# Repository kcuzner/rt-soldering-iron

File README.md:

# RT Soldering Iron
By Kevin Cuzner

**NOTE: THIS IS A WORK IN PROGRESS AND MAY NEVER BE COMPLETED**

## Objective

The Weller RT Soldering Iron Tips are $20-$30 apiece. They are rated to about
55W and many variants come to a very fine point. I had the pleasure of using one
of these soldering irons at my university, but the base stations cost several
hundred dollars. This project aims to build a "base station" of sorts for these
tips so that I can use them without needing to purchase a real base station.

Note that this project has been done before, but I'm doing it myself because
reasons.

## Concept

- The Weller RT soldering iron tips have a 1/8" audio plug which has ground,
  heater, and thermocouple contacts.
- The heater can be powered from 12V and will consume 55W.
- Without closed loop control, the soldering iron tip will quickly burn itself
  up.
- This driver board will provide 12V and closed loop heater control.
- The driver board has a 1/8" audio jack on one end and a barrel jack on the
  other. It is short enough and skinny enough so that it can be mounted directly
  to the tip and become part of the handpiece, with the barrel jack connecting
  to the 12V power supply.

## Builds

### Rev A Deviations

### Rev B Deviations

- 490-14603-1-ND (0.1uF 0402 25V 10% cap) was unavailable. No lead time.
  Ordered 490-13341-1-ND (0.1uf 0402 25V 20% cap) instead.
- Accelerometer was out of stock (again...). The other variant used on the LED
  watch was out of stock too. Did not order this time around.

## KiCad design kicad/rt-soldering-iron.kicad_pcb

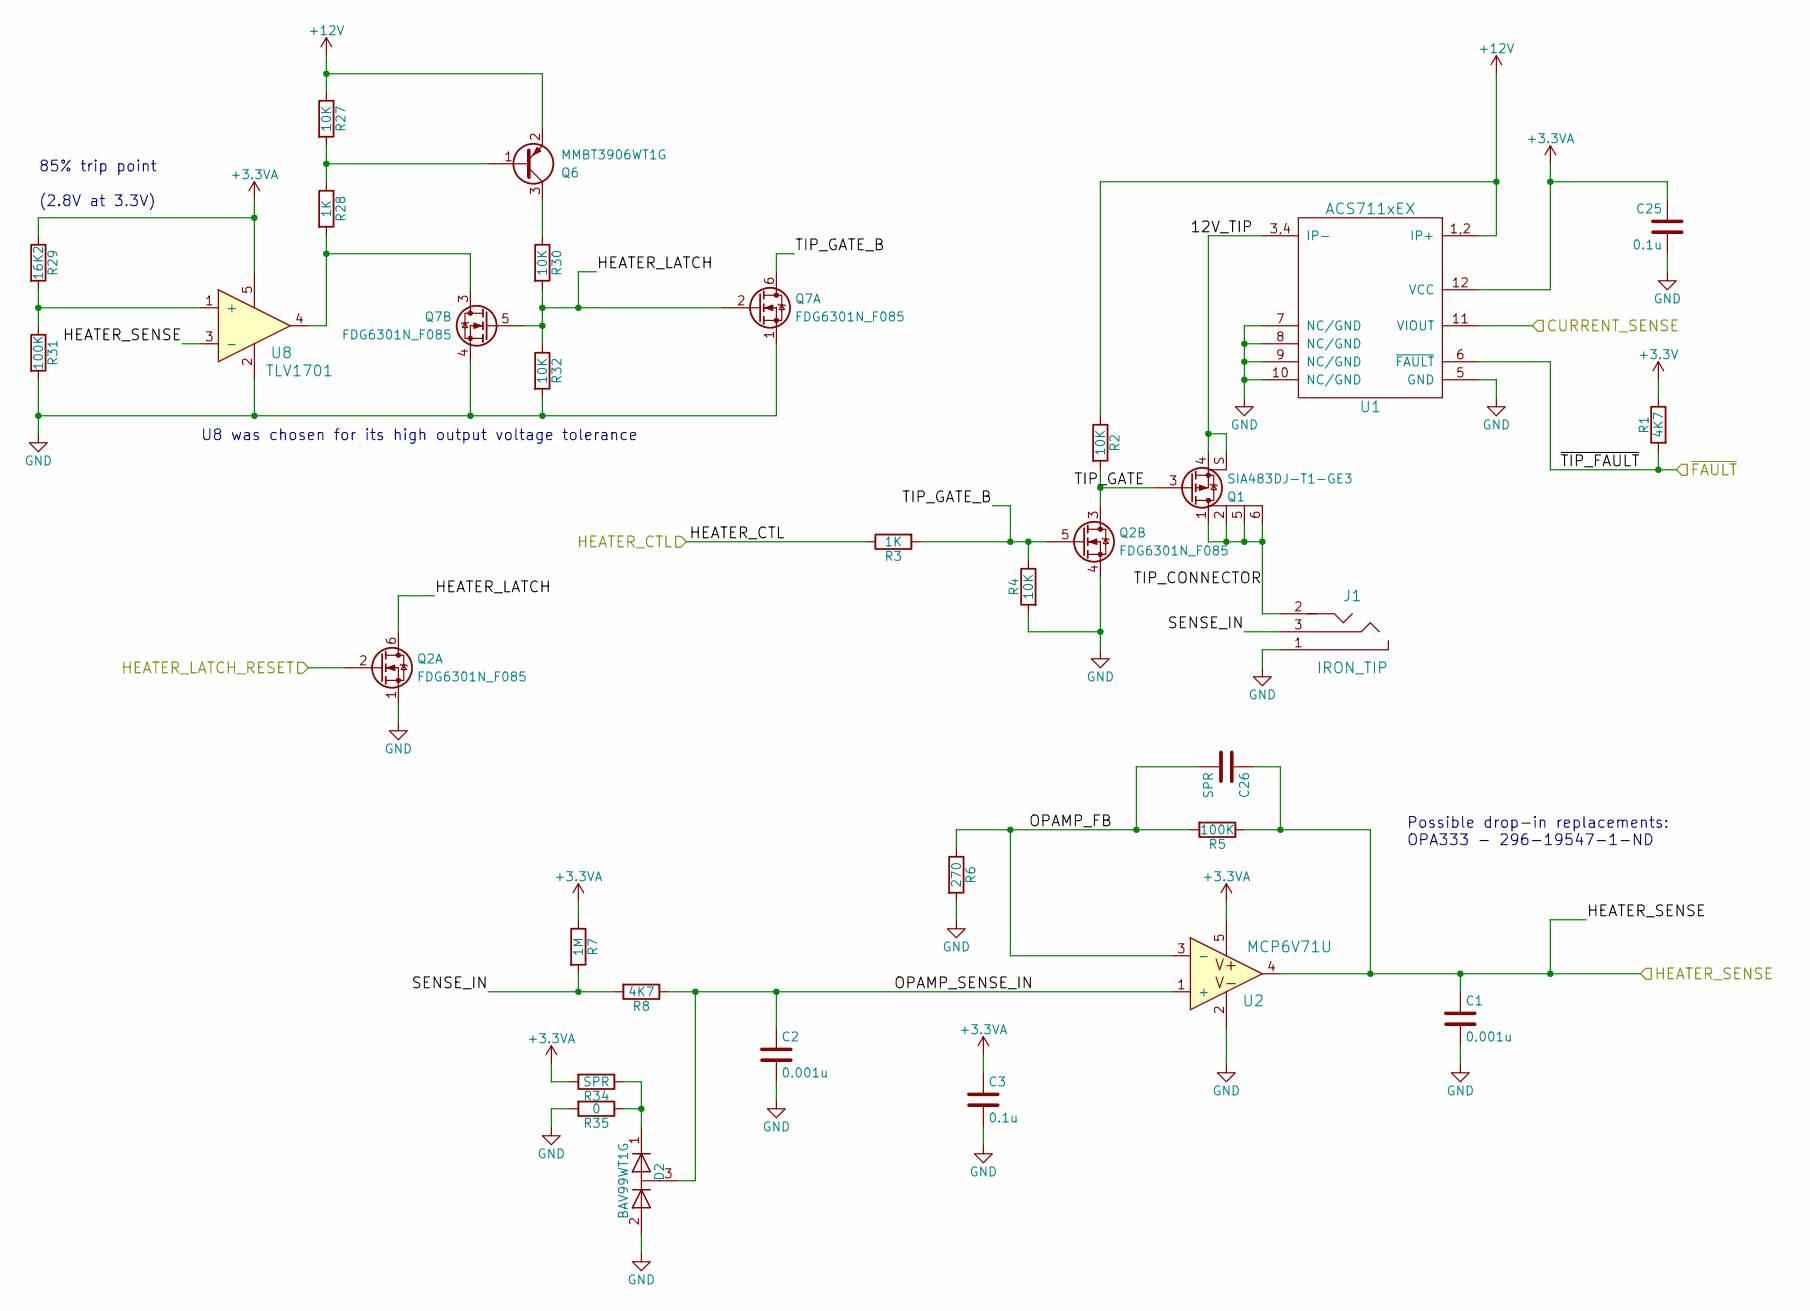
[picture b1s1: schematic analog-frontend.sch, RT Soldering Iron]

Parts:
C1, C2: 0.001u; C_0402; Part No. 1276-1057-1-ND
C3, C25: 0.1u; C_0402; Part No. 490-14603-1-ND
C26: SPR; C_0402
D2: BAV99WT1G; SOT-323_SC-70; Part No. BAV99WT1GOSCT-ND
J1: IRON_TIP; SJ-3502-SMT; Part No. CP-3502SJCT-ND
Q1: SIA483DJ-T1-GE3; PP-SC70-6L; Part No. SIA483DJ-T1-GE3CT-ND
Q2, Q7: FDG6301N_F085; SOT-363_SC-70-6; Part No. FDG6301N-F085CT-ND
Q6: MMBT3906WT1G; SOT-323_SC-70; Part No. MMBT3906WT1GOSCT-ND
R1, R8: 4K7; R_0402; Part No. 311-4.7KLRCT-ND
R2, R4, R27, R30, R32: 10K; R_0402; Part No. 311-10.0KLRCT-ND
R3, R28: 1K; R_0402; Part No. 311-1.0KJRCT-ND
R5, R31: 100K; R_0402; Part No. RR05P100KDCT-ND
R6: 270; R_0402; Part No. RR05P270DCT-ND
R7: 1M; R_0402; Part No. 311-1.00MLRCT-ND
R29: 16K2; R_0402; Part No. 311-2144-1-ND
R34: SPR; R_0402
R35: 0; R_0402; Part No. 311-0.0JRCT-ND
U1: ACS711xEX; 12-WFQFN; Part No. 620-1483-1-ND
U2: MCP6V71U; SOT-353_SC-70-5; Part No. MCP6V71UT-E/LTYCT-ND
U8: TLV1701; SOT-353_SC-70-5; Part No. 296-40599-1-ND

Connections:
+3.3VA: C3.1, C25.1, R7.1, R29.1, R34.2, U1.12 (VCC), U2.5, U8.5; also elsewhere on the board
+3V3: R1.1; also elsewhere on the board
+12V: Q6.2 (E), R2.1, R27.1, U1.1,2 (IP+); also elsewhere on the board
/Analog Frontend/12V_TIP: Q1.4 (S), Q1.S, U1.3,4 (IP-)
/Analog Frontend/CURRENT_SENSE: U1.11 (VIOUT); also elsewhere on the board
/Analog Frontend/HEATER_CTL: R3.1; also elsewhere on the board
/Analog Frontend/HEATER_LATCH: Q2.6 (D), Q7.2 (G), Q7.5 (G), R30.2, R32.1
/Analog Frontend/HEATER_LATCH_RESET: Q2.2 (G); also elsewhere on the board
/Analog Frontend/HEATER_SENSE: C1.1, C26.1, R5.1, U2.4, U8.3 (-); also elsewhere on the board
/Analog Frontend/OPAMP_FB: C26.2, R5.2, R6.1, U2.3 (-)
/Analog Frontend/OPAMP_SENSE_IN: C2.1, D2.3 (common), R8.1, U2.1 (+)
/Analog Frontend/SENSE_IN: J1.3, R7.2, R8.2
/Analog Frontend/TIP_CONNECTOR: J1.2, Q1.1 (D), Q1.2 (D), Q1.5 (D), Q1.6 (D)
/Analog Frontend/TIP_GATE: Q1.3 (G), Q2.3 (D), R2.2
/Analog Frontend/TIP_GATE_B: Q2.5 (G), Q7.6 (D), R3.2, R4.1
/Analog Frontend/~FAULT: R1.2, U1.6 (~FAULT); also elsewhere on the board
GND: C1.2, C2.2, C3.2, C25.2, D2.2 (A), J1.1, Q2.1 (S), Q2.4 (S), Q7.1 (S), Q7.4 (S), R4.2, R6.2, R31.2, R32.2, R35.2, U1.5 (GND), U1.7 (NC/GND), U1.8 (NC/GND), U1.9 (NC/GND), U1.10 (NC/GND), U2.2, U8.2; also elsewhere on the board
unnamed: D2.1 (K), R34.1, R35.1
unnamed: Q6.1 (B), R27.2, R28.1
unnamed: Q6.3 (C), R30.1
unnamed: Q7.3 (D), R28.2, U8.4
unnamed: R29.2, R31.1, U8.1 (+)

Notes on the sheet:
Possible drop-in replacements: OPA333 - 296-19547-1-ND
85% trip point (2.8V at 3.3V)
U8 was chosen for its high output voltage tolerance

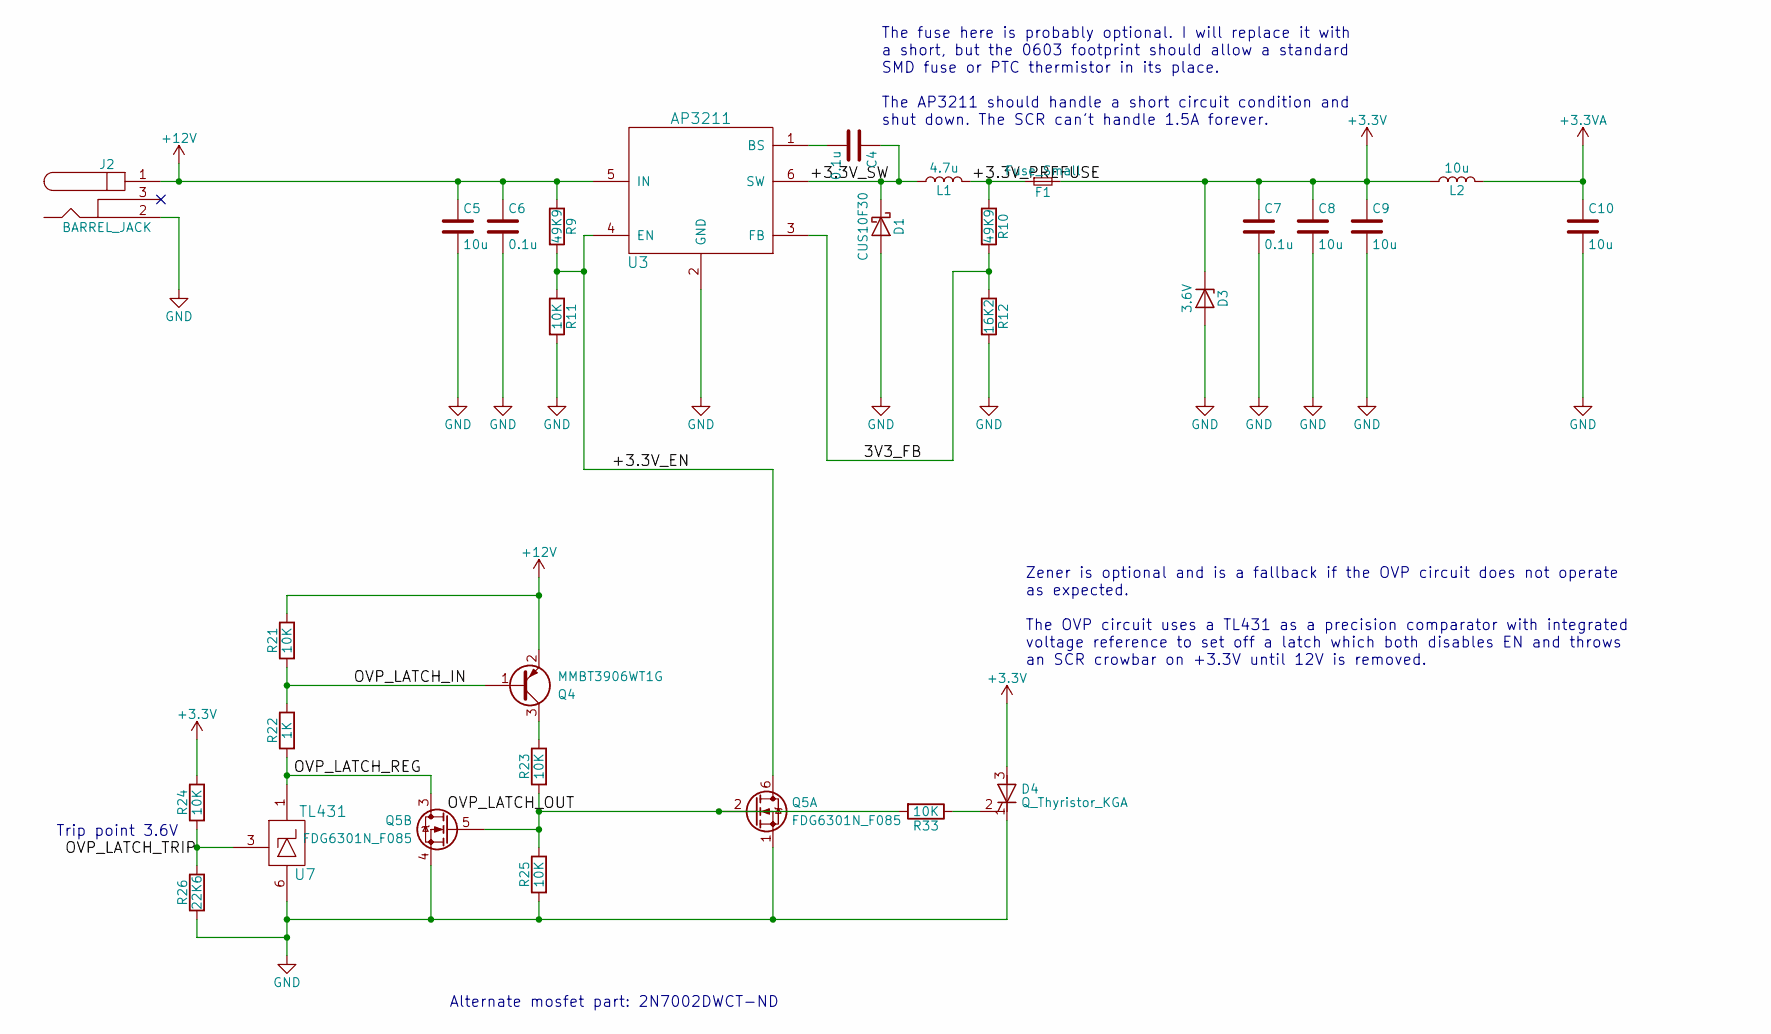
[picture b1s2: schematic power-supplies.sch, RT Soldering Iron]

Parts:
C4, C6, C7: 0.1u; C_0402; Part No. 490-14603-1-ND
C5: 10u; C_0603; Part No. 490-7202-1-ND
C8, C9, C10: 10u; C_0402; Part No. 1276-6830-1-ND
D1: CUS10F30; D_SOD-323; Part No. CUS10F30H3FCT-ND
D3: 3.6V; D_SOD-523; Part No. DZ2S036M0LCT-ND
D4: Q_Thyristor_KGA; SOT-23; Part No. NYC0102BLT1GOSCT-ND
F1: Fuse_Small; R_0603
J2: BARREL_JACK; PJ-069B-SMT; Part No. CP-069BPJCT-ND
L1: 4.7u; Inductor_Taiyo-Yuden_NR-30xx; Part No. 587-2591-1-ND
L2: 10u; R_0805; Part No. 445-6396-1-ND
Q4: MMBT3906WT1G; SOT-323_SC-70; Part No. MMBT3906WT1GOSCT-ND
Q5: FDG6301N_F085; SOT-363_SC-70-6; Part No. FDG6301N-F085CT-ND
R9, R10: 49K9; R_0402; Part No. 311-2296-1-ND
R11, R21, R23, R24, R25, R33: 10K; R_0402; Part No. 311-10.0KLRCT-ND
R12: 16K2; R_0402; Part No. 311-2144-1-ND
R22: 1K; R_0402; Part No. 311-1.0KJRCT-ND
R26: 22K6; R_0402; Part No. YAG3061CT-ND
U3: AP3211; SOT-23-6; Part No. AP3211KTR-G1DICT-ND
U7: TL431; SOT-363_SC-70-6; Part No. 296-17863-1-ND

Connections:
+3.3VA: C10.1, L2.2; also elsewhere on the board
+3V3: C7.1, C8.1, C9.1, D3.1 (K), D4.3 (A), F1.2, L2.1, R24.1; also elsewhere on the board
+12V: C5.1, C6.1, J2.1, Q4.2 (E), R9.1, R21.1, U3.5 (IN); also elsewhere on the board
/Power Supplies/3V3_FB: R10.2, R12.1, U3.3 (FB)
/Power Supplies/+3.3V_EN: Q5.6 (D), R9.2, R11.1, U3.4 (EN)
/Power Supplies/+3.3V_PREFUSE: F1.1, L1.2, R10.1
/Power Supplies/+3.3V_SW: C4.1, D1.1 (K), L1.1, U3.6 (SW)
/Power Supplies/OVP_LATCH_IN: Q4.1 (B), R21.2, R22.1
/Power Supplies/OVP_LATCH_OUT: Q5.2 (G), Q5.5 (G), R23.2, R25.1, R33.2
/Power Supplies/OVP_LATCH_REG: Q5.3 (D), R22.2, U7.1
/Power Supplies/OVP_LATCH_TRIP: R24.2, R26.1, U7.3
GND: C5.2, C6.2, C7.2, C8.2, C9.2, C10.2, D1.2 (A), D3.2 (A), D4.1 (K), J2.2, Q5.1 (S), Q5.4 (S), R11.2, R12.2, R25.2, R26.2, U3.2 (GND), U7.6; also elsewhere on the board
unnamed: C4.2, U3.1 (BS)
unnamed: D4.2 (G), R33.1
unnamed: Q4.3 (C), R23.1

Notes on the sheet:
Trip point 3.6V
Zener is optional and is a fallback if the OVP circuit does not operate as expected. The OVP circuit uses a TL431 as a precision comparator with integrated voltage reference to set off a latch which both disables EN and throws an SCR crowbar on +3.3V until 12V is removed.
Alternate mosfet part: 2N7002DWCT-ND
The fuse here is probably optional. I will replace it with a short, but the 0603 footprint should allow a standard SMD fuse or PTC thermistor in its place. The AP3211 should handle a short circuit condition and shut down. The SCR can't handle 1.5A forever.

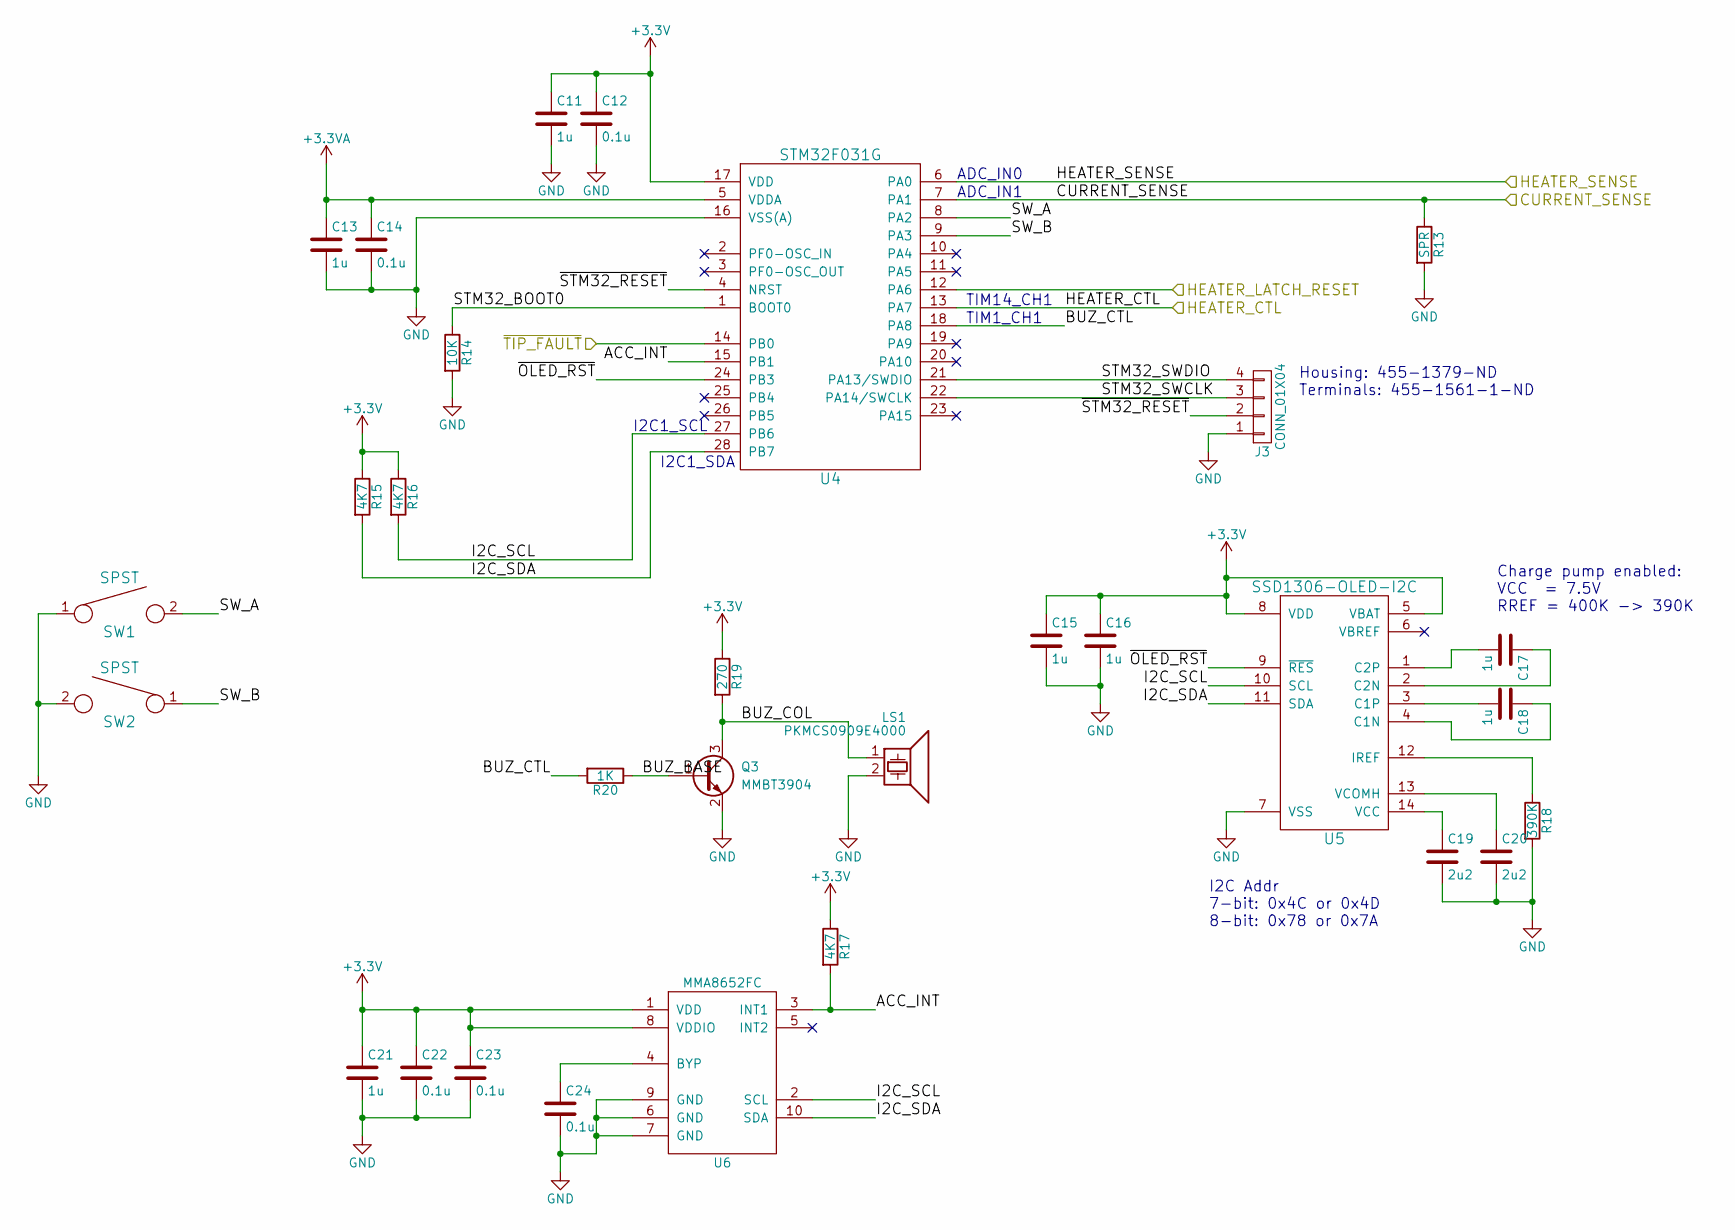
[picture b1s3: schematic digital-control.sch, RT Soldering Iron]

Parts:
C11, C13, C15, C16, C17, C18, C21: 1u; C_0402; Part No. 490-10018-1-ND
C12, C14, C22, C23, C24: 0.1u; C_0402; Part No. 490-14603-1-ND
C19, C20: 2u2; C_0402; Part No. 490-13234-1-ND
J3: CONN_01X04; JST-SH-4; Part No. 455-1790-1-ND
LS1: PKMCS0909E4000; Murata-PKMCS; Part No. 490-9647-1-ND
Q3: MMBT3904; SOT-323_SC-70; Part No. MMBT3904WT1GOSCT-ND
R13: SPR; R_0402
R14: 10K; R_0402; Part No. 311-10.0KLRCT-ND
R15, R16, R17: 4K7; R_0402; Part No. 311-4.7KLRCT-ND
R18: 390K; R_0402; Part No. 311-390KJRCT-ND
R19: 270; R_0402; Part No. RR05P270DCT-ND
R20: 1K; R_0402; Part No. 311-1.0KJRCT-ND
SW1, SW2: SPST; Panasonic_EVQP4; Part No. P15502CT-ND
U4: STM32F031G; 28-UFQFPN; Part No. 497-13619-ND
U5: SSD1306-OLED-I2C; OLED-FPC-I2C
U6: MMA8652FC; 10-DFN; Part No. MMA8652FCR1CT-ND

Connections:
+3.3VA: C13.1, C14.1, U4.5 (VDDA); also elsewhere on the board
+3V3: C11.1, C12.1, C15.1, C16.1, C21.1, C22.1, C23.1, R15.1, R16.1, R17.1, R19.1, U4.17 (VDD), U5.5 (VBAT), U5.8 (VDD), U6.1 (VDD), U6.8 (VDDIO); also elsewhere on the board
/Analog Frontend/CURRENT_SENSE: R13.1, U4.7 (PA1); also elsewhere on the board
/Analog Frontend/HEATER_CTL: U4.13 (PA7); also elsewhere on the board
/Analog Frontend/HEATER_LATCH_RESET: U4.12 (PA6); also elsewhere on the board
/Analog Frontend/HEATER_SENSE: U4.6 (PA0); also elsewhere on the board
/Analog Frontend/~FAULT: U4.14 (PB0); also elsewhere on the board
/Digital Control/ACC_INT: R17.2, U4.15 (PB1), U6.3 (INT1)
/Digital Control/BUZ_BASE: Q3.1 (B), R20.1
/Digital Control/BUZ_COL: LS1.1, Q3.3 (C), R19.2
/Digital Control/BUZ_CTL: R20.2, U4.18 (PA8)
/Digital Control/I2C_SCL: R16.2, U4.27 (PB6), U5.10 (SCL), U6.2 (SCL)
/Digital Control/I2C_SDA: R15.2, U4.28 (PB7), U5.11 (SDA), U6.10 (SDA)
/Digital Control/STM32_BOOT0: R14.1, U4.1 (BOOT0)
/Digital Control/STM32_SWCLK: J3.3, U4.22 (PA14/SWCLK)
/Digital Control/STM32_SWDIO: J3.4, U4.21 (PA13/SWDIO)
/Digital Control/SW_A: SW1.2, U4.8 (PA2)
/Digital Control/SW_B: SW2.1, U4.9 (PA3)
/Digital Control/~OLED_RST: U4.24 (PB3), U5.9 (~RES)
/Digital Control/~STM32_RESET: J3.2, U4.4 (NRST)
GND: C11.2, C12.2, C13.2, C14.2, C15.2, C16.2, C19.2, C20.2, C21.2, C22.2, C23.2, C24.2, J3.1, J3.NC, LS1.2, Q3.2 (E), R13.2, R14.2, R18.2, SW1.1, SW2.2, U4.16 (VSS(A)), U5.7 (VSS), U6.6 (GND), U6.7 (GND), U6.9 (GND); also elsewhere on the board
unnamed: C17.1, U5.2 (C2N)
unnamed: C17.2, U5.1 (C2P)
unnamed: C18.1, U5.4 (C1N)
unnamed: C18.2, U5.3 (C1P)
unnamed: C19.1, U5.14 (VCC)
unnamed: C20.1, U5.13 (VCOMH)
unnamed: C24.1, U6.4 (BYP)
unnamed: R18.1, U5.12 (IREF)

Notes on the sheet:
I2C Addr 7-bit: 0x4C or 0x4D 8-bit: 0x78 or 0x7A
Housing: 455-1379-ND Terminals: 455-1561-1-ND
ADC_IN0
TIM14_CH1
I2C1_SCL
I2C1_SDA
Charge pump enabled: VCC = 7.5V RREF = 400K -> 390K
ADC_IN1
TIM1_CH1

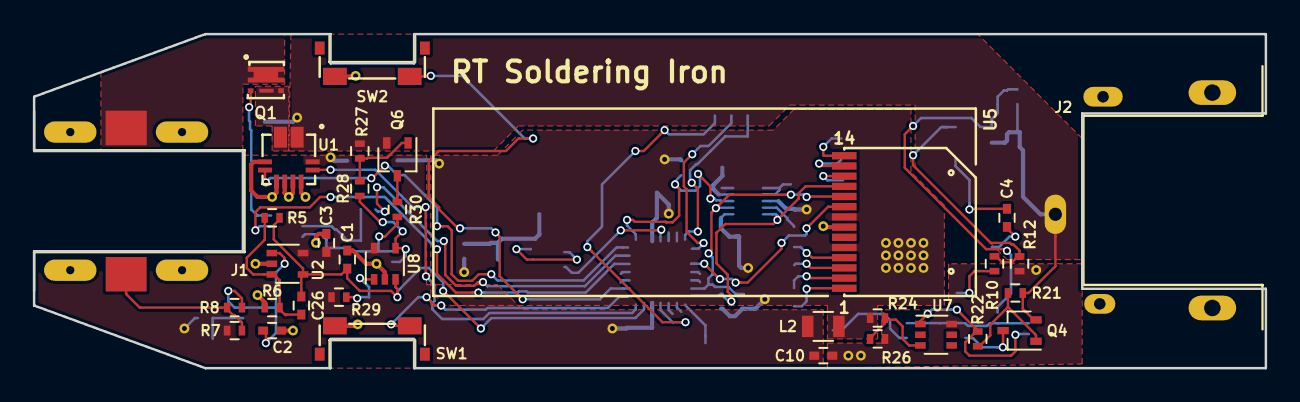
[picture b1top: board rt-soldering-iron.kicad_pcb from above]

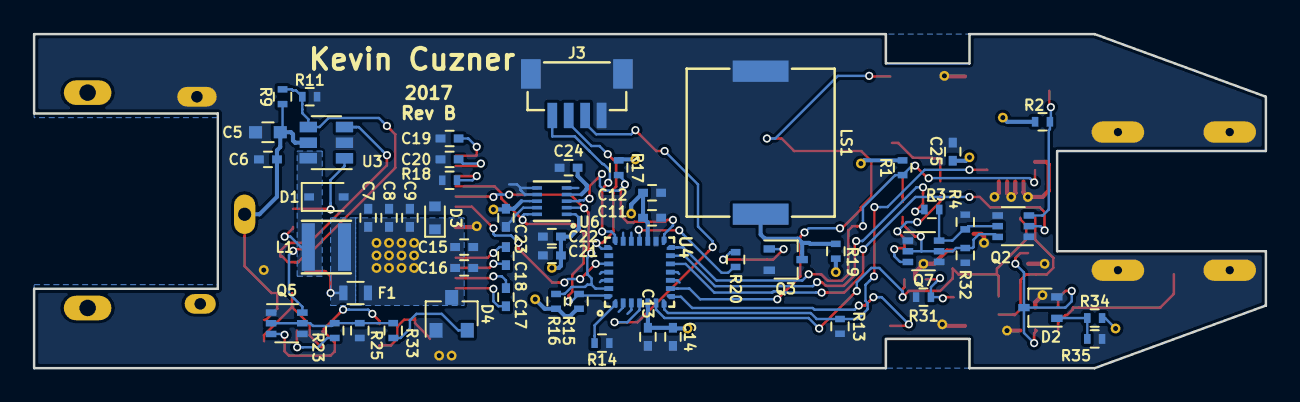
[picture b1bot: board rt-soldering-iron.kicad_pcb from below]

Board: 2 copper layers, 74.9 x 20.3 mm, 89 parts (56 on the bottom side), 54 nets.

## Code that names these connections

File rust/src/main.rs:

//! Firmware for the rt soldering iron

#![feature(used, const_fn, asm, naked_functions, const_size_of, const_unsafe_cell_new, const_ptr_null_mut, never_type, generators, generator_trait)]
#![no_main]
#![no_std]

extern crate cortex_m;
#[macro_use]
extern crate cortex_m_rt;
extern crate bare_metal;
extern crate panic_abort;
extern crate embedded_hal;
extern crate stm32f031x;
extern crate stm32f031x_hal;
extern crate board_support as bs;
extern crate nb_sync;
#[macro_use(await)]
extern crate nb;
extern crate cast;
extern crate fpa;
extern crate numtoa;

extern crate bare_take_mut as take_mut;

use core::ops::Generator;
use core::str::{from_utf8_unchecked, from_utf8_unchecked_mut};

use embedded_hal::PwmPin;

use numtoa::NumToA;
use cast::u16;
use fpa::I16F16;

use stm32f031x_hal::rcc::RccExt;
use stm32f031x_hal::time::{U32Ext};
use stm32f031x_hal::flash::{FlashExt};
use stm32f031x_hal::gpio::GpioExt;
use stm32f031x_hal::i2c::{I2CExt, IntoScl, IntoSda, I2cTiming, I2cTimingSetting};
use stm32f031x_hal::adc::{AdcExt, IntoAnalog};
use stm32f031x_hal::pwm::{PwmExt, IntoPwm};

pub use bs::{TIM1_BRK_UP_IRQ, SysTick};
pub use debug::{HARD_FAULT_STACK};

mod debug;
mod font;
mod gfx;
mod pid;

#[derive(Copy, Clone)]
struct DisplayData {
    adc: u32,
    pid: u32,
}

impl DisplayData {
    pub fn new(adc: u32, pid: u32) -> Self {
        DisplayData { adc: adc, pid: pid }
    }
}

/// Performs an integer to hex conversion
///
/// Requires an &str of at least 8 bytes length
fn hex(value: u32, out: &mut str) {
    unsafe {
        let bytes = out.as_bytes_mut();
        for i in 0..8 {
            let shift = i * 4;
            let mask = 0xF0000000 >> shift;
            let nibble = ((value & mask) >> 28 - shift) as u8;
            bytes[i] = match nibble {
                0...9 => b'0' + nibble,
                10...15 => b'A' + (nibble - 10),
                _ => b'Z',
            }
        }
    }
}

fn test() -> ! {
    let core_peripherals = stm32f031x::CorePeripherals::take().unwrap();
    let peripherals = stm32f031x::Peripherals::take().unwrap();
    let mut syst = core_peripherals.SYST;
    let mut nvic = core_peripherals.NVIC;
    let mut rcc = peripherals.RCC.constrain();
    let mut gpioa = peripherals.GPIOA.split(&mut rcc.ahb);
    let mut gpiob = peripherals.GPIOB.split(&mut rcc.ahb);
    let mut flash = peripherals.FLASH.constrain();
    let mut uncalibrated_adc = peripherals.ADC.constrain(&mut rcc.apb2);
    let tim1 = peripherals.TIM1;
    let tim14 = peripherals.TIM14;

    // Display queue
    let mut buf: [Option<DisplayData>; 4] = [None, None, None, None];
    let mut chan = nb_sync::fifo::Channel::new(&mut buf);
    let (mut receiver, mut sender) = chan.split();

    // Set up the clocks
    rcc.cfgr = rcc.cfgr.sysclk(48.mhz())
        .hclk(48.mhz())
        .pclk(8.mhz());
    let clocks = rcc.cfgr.freeze(&mut flash.acr);

    // Calibrate the system tick for 1 ms
    bs::systick::calibrate(&mut syst, clocks.clone());

    // Create the I2C master
    let i2c = peripherals.I2C1.constrain(&mut rcc.apb1)
        .bind(gpiob.pb6.into_scl(&mut gpiob.regs), gpiob.pb7.into_sda(&mut gpiob.regs))
        .master(I2cTiming::from(I2cTimingSetting::Fast));

    // Create the buzzer
    let mut buzzer = bs::Buzzer::new(tim1, &mut rcc.apb2, &mut nvic, gpioa.pa8, &mut gpioa.regs);

    // Create the heater sense line
    let mut heater_sense = gpioa.pa0.into_analog_input(&mut gpioa.regs);

    // Create the SSD1306
    let mut ssd1306_reset = bs::ssd1306::Uninitialized::new(i2c, bs::ssd1306::SSD1306Address::Low, gpiob.pb3, &mut gpiob.regs).reset();

    // Create the heater PWM
    let mut heater_pwm = tim14.constrain_pwm(&mut rcc.apb1);
    let mut heater_pin = heater_pwm.ch1(gpioa.pa7.into_pwm(&mut gpioa.regs));

    // Create the heater controller
    heater_pin.set_duty(0);
    heater_pwm.set_period(clocks.clone(), 1.khz());
    heater_pwm.enable();
    heater_pwm.commit();
    heater_pin.enable();
    let mut heater_pid = pid::PID::new(pid::Constants::new(0.2f64, 0.1f64, 0.001f64), heater_pin);

    // Build a setpoint using fixed point arithmetic
    //let c_per_bit = I16F16(0.053618f64).unwrap(); //based on seebeck and bad assumptions
    let c_per_bit = I16F16(0.13431f64).unwrap(); //based on 500C = 3.0V calculation
    //let bits_per_c = I16F16(18.650f64).unwrap();
    let bits_per_c = I16F16(7.4455f64).unwrap();
    let setpoint = u16(I16F16(300i16) * bits_per_c).unwrap();

    // UI task
    let mut ui_fn = || {
        let mut ssd1306_init = await!(ssd1306_reset.poll()).unwrap().initialize(ssd1306_reset);
        let mut display_write = await!(ssd1306_init.poll()).unwrap().commit(ssd1306_init);
        buzzer.beep(100, 1000.hz(), clocks.clone());
        let mut now = bs::systick::now();
        let mut y = 0;
        let mut x = 0;
        loop {
            now = await!(bs::systick::wait_until(now + 100)).unwrap();
            let display_data = await!(receiver.recv()).unwrap();
            let mut display = await!(display_write.poll()).unwrap().finish(display_write);
            display.clear();
            let font = font::Font::EightByEight;
            let mut arr: [u8; 8] = [0; 8];
            {
                let c = I16F16(display_data.adc).unwrap() * c_per_bit;
                let start_index = u16(c).unwrap().numtoa(10, &mut arr);
                let string = unsafe { from_utf8_unchecked(&arr[start_index..]) };
                font.render_string(&string, gfx::Point::new(0, 0), &mut display).unwrap();
            }
            {
                let mut string = unsafe { from_utf8_unchecked_mut(&mut arr) };
                hex(display_data.pid, &mut string);
                font.render_string(&string, gfx::Point::new(0, 12), &mut display).unwrap();
            }
            display.hline(0, y, 127).unwrap();
            display.vline(x, 0, 31).unwrap();
            y += 1;
            if y >= 32 {
                y = 0;
            }
            x += 1;
            if x >= 128 {
                x = 0;
            }
            display_write = display.commit();
        }
    };

    // Control task
    let mut adc_fn = || {
        let mut calibrated_adc = await!(uncalibrated_adc.poll()).unwrap().finish(uncalibrated_adc);
        loop {
            let mut conversion = calibrated_adc.single(heater_sense);
            let (adc, hs, value) = await!(conversion.poll()).unwrap().finish(conversion);
            let pid_output = heater_pid.step(setpoint, value.raw_right() as u16);
            heater_pwm.commit();
            let data = DisplayData::new(value.raw_right(), pid_output.into());
            //yuck. Send inside a vanilla await! requires Copy.
            match sender.send(data) {
                _ => ()
            };
            await!(sender.send(data)).unwrap();
            calibrated_adc = adc;
            heater_sense = hs;
        }
    };

    // Dummy task for fun
    let mut incr_fn = || {
        let mut now = bs::systick::now();
        loop {
            now = await!(bs::systick::wait_until(now + 100)).unwrap();
            /*{
                let mut string = await!(shared_value.lock()).unwrap();
                unsafe {
                    let bytes = string.as_bytes_mut();
                    bytes[0] += 1;
                    if bytes[0] > b'Z' {
                        bytes[0] = b'A';
                    }
                }
            }*/
        }
    };
    loop {
        unsafe { ui_fn.resume() };
        unsafe { adc_fn.resume() };
        unsafe { incr_fn.resume() };
    }
}

entry!(main);

fn main() -> ! {
    test()
}

exception!(HardFault, debug::hard_fault_handler);
exception!(*, default_handler);

fn default_handler(_irqn: i16) {
    panic!();
}

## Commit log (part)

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2017-05-31 Initial commit
    First pass at placement
2017-06-01 Added buzzer, fixed footprint errors, and updated silkscreen
    The board is probably ready to be ordered
2017-06-03 Changed out the op amp and fixed oval holes for OSHPark
    I don't think I'm going to go with OSHPark. It seems they can't
    fabricate this thing.
2017-06-15 Added initial firmware and flashing utilities
    The device is programmable as is on the PCB. Hooray!!
2017-06-18 Removed heap, fixed startup delay issue, added ssd1306 initialization
    The startup delay issue had to do with a problem in the port. It didn't
    reset the current value of the systick timer, meaning that it had to
    wait until it counted all the way down before the first tick would get
    executed. It turns out that this is just about a second on this
    processor running that the default speed. Resetting the CVR fixed this
    issue and now delays work fine if they occur within the first second of
2017-06-18 Added SSD1306 display routine, increased I2C speed
    The display is able to send the buffer in about 45ms. This could
    probably be increased somewhat, but it is sufficiently fast for now.
2017-06-22 Added IRQHandler template and changed isr getter to constexpr
    The static isr(IRQn) function was changed to a constexpr. This reduced
    the code size slightly, but I'm not sure the gains will last when more
    IRQHandlers are added.
    The template class is a quick and easy way to make a class be able to
    handle multiple ISRs at the expense of more code space.
2017-06-29 Fixed schematic to use USLetter paper
2017-07-01 Started second revision, added a comparator and eFuse
    The comparator has no hysteresis in its current configuration, so that
    will need to be fixed.
2017-07-01 Fixed buzzer mode setting
2017-07-03 Added display blit routine
    It is not time efficient, but has fairly small code.
2017-07-15 Added font and line drawing capabilities
    The font is pulled from the local machine. It is a bit rough, so I might
    just have to make one manually
2017-08-05 Started restructuring code for actual program
2017-08-20 Removed comp, efuse. Added zener protection. Fixed OLED footprint.
    I may have destroyed a board by shorting the FB pin to ground. I left
    off the zener protection on Rev A. Never again.
2017-08-20 Added overvoltage protection circuit to +3.3V
    Part selection is complete. There are things without part numbers.
    It uses a TL431 as a precision comparator with integrated voltage
    reference to activate a latch which both shuts down the regulator and
    throws a crobar across +3.3V. There is also space for a fuse on +3.3V
    (I'm thinking a PTC resettable fuse could go there, but I'm not sure
    what the tradeoffs are for that).
2017-08-31 Added overtemperature latching circuit with reset
    This uses a comparator to trigger the same latch type that is used on
    the OVP circuit.
2017-09-01 Fixed thermal cutoff circuit and finished footprint selection
    The main issue with the thermal cutoff was the open-collector maximum
    voltage. I had to find a (slightly more expensive) comparator with an
    output that was tolerant. Other comparators that would be instead
    tolerant of being run off 12V were about the same price.
    The fuse I'm not sure about. I'm just going to short it out. The
    regulator can handle a short circuit and so can the crowbar. I also
2017-09-23 Finished placement of all parts. Routed power supply.
    The board has been shrunk by 10mm or so. The elimination of the giant
    directional switch is the reason this is even possible.
2017-09-23 Completed initial routing
2017-09-23 Initial silkscreen fixing
2017-09-23 Added tags to unused QFN pins except on accelerometer
2017-10-15 Fixed some capacitor footprints
2017-10-16 Added initial cutouts for the oval pins
2017-10-16 Storing Rev A Gerbers
2017-10-16 Created Rev B Gerbers
2017-10-16 Created gerbv project for viewing the gerbers
2017-11-07 Updated parts for rev B parts order, updated dates
2017-11-27 Added simulation of the OVP latch circuit
    Turns out, just a static simulation isn't enough. The simulation needs
    to test ramp-up explicitly. Requires that the TL431 model be added (the
    HSPICE model works with LTSpice in this case, surprisingly).
2017-11-27 Fixed a really dumb part number mistake on the comparator
    The comparator part number is ths SOT23 footprint. I had planned for the
    SC-70 footprint. I bought the wrong footprint...
2017-11-27 Adding sparse readme
2018-02-06 (WIP) Started writing scheduler and pendsv interrupt
2018-02-06 Split out RTOS into separate modules
2018-02-06 (WIP) Starting figuring out how an RTOS would work in rust
    It does not go well, but that's because this probably isn't the best
    project to learn rust on...
2018-02-06 Fixed test program to buzz the buzzer
2018-02-06 Made some progress on a structure
    However, I'm pretty sure that this will not work. The storing and
    restoring of the context requires knowledge of the stack frame if I'm to
    do it efficiently.
2018-02-06 Fixed two silly mistakes, a sign switch and a missing mut
    The sign switch resulted in a hard fault. The missing mut probably would
    have also caused a hard fault (since the stack got located in rodata),
    but its fixed now.
2018-02-06 Changed tasks to start leaning towards an unallocated stack
    The way this is going to work is once the scheduler is initiated, the
    current stack pointer will be noted. All of the configured tasks will
    then have their stacks allocated in the remaining stack space. I've
    decided on this method since syntactically it looks simpler.
    To prevent stack overflow issues, I'd like some way to allocate fake
    space in the linker file for all the stacks to ensure that everything
2018-02-06 Added initial bare firmware, based on japaric's cortex-m crate
2018-02-06 Added hard fault debugger
    Basically just breaks the NVIC state out into a visible struct. In the
    future I might make it act like the one I have for the C firmware.
2018-02-06 Added feature for const size_of
2018-02-06 Added a test buzzing program using the new RTOS. It works!!
2018-02-06 Added rudimentary flashing script
2018-02-06 Cleanup after adding flashing method to embedded.py
2018-02-06 Started adding some enums to the stm32f031x svd
2018-02-06 Fixed PENDSV ISR to actually compile
    Since we are using the main stack pointer always and not switching (for
    now), we can use the standard push and pop instructions. This avoids the
    need for that pesky SUB which I couldn't quite get to compile.
2018-02-06 Added stm32f031x support package
2018-02-06 Added buzzer initialization as a test
2018-02-06 Started adding some synchronization entities (untested)
    The plan right now is to implement a semaphore, queue, and tick-waiter
    and build off of that.
    Also added a readme with the basic gist of the RTOS
2018-02-11 Changed Block trait to no longer use static lifetimes
    This really causes usability problems because any function receiving the
    reference is free to operate directly on the Block forever. We don't
    actually want that. It's like we want to force a static lifetime of the
    reference, but not promise to use it. I don't really know of a good way
    to enforce this, so instead I just made a UniqueId struct based on
    UnsafeCell which creates an atomically incrementing UniqueId.
2018-02-26 Restructured RTOS into a separate crate
2018-02-26 Restructured project further, creating a components directory
2018-03-02 Created scaffold for HAL with working RCC component
    So exciting...
2018-03-08 Changed alternate functions to be concrete types
    This should allow for using traits to denote that a particular pin in a
    particular alternate function mode can be used in a specific way. It
    also is safer since not all pins implement all alternate functions.
2018-03-31 Upgraded cortex-m-rt so that it will compile with the latest nightly
2018-03-31 Initial I2C abstraction implementation using nb
    Note that right now CMD has to be immovable so that the compiler doesn't
    freak about about the Generator referencing something on its own stack
    (self-referential struct). There should be a way to fix this, but I'm
    still reading the docs.
2018-04-01 Restructured GPIO and added output-od-pu mode
    The DRY level is much smaller and it should be simpler to add new output
    modes now. However, the code is quite dangerous as the values passed
    into my new configure function may not match the requested output type.
    It is effectively a thin wrapper around the register writes.
2018-04-08 Fixed various bugs relating to timing
2018-04-08 Added separate board support crate and systick wrapper
    The systick wrapper now allows for some non-deterministic timing to
    occur (i.e. 'wait roughly 1/2 second').
2018-04-12 Changed I2C implementation to eliminate data borrows
2018-04-13 Added several ways of declaring SSD1306 commands
    I can't decide...
2018-04-23 Added (untested) initialization structure and methods for buffer mods
2018-04-30 Created a static slice writer in the I2C peripheral
2018-05-01 Added API for committing the display and a test animation
2018-05-01 Fixed some truncation bugs in the hline and vline methods
    Apparently C coerces these to be larger
2018-05-08 Added basic bitmap and font rendering capabilities
    Currently, I only have an 8x8 IBM font. I need to get a 16x16 font for
    the numbers and I'll be golden.
2018-05-08 Added scaffold for a sync crate based on nb
2018-05-08 Added a quick and primitive mutex
    It is quite untested...
2018-05-08 Added test and fixed a couple problems with the mutex
    Now, it's not a very good test. If the locking logic is wrong we'll have
    a problem. However, this is going to be used really only for display and
    UI communication with the main heater control loop, so it isn't critical
    if it is out of sync occasionally.
2018-05-09 Started building a continuous conversion framework
2018-05-09 Added initial single-shot ADC implementation
    I haven't confirmed that it works yet...
2018-05-10 Fixed AdcValue conversions and hex function
2018-05-10 Cleaning warnings from ADC
2018-05-10 Cleaned warnings and disabled RTOS component craet
2018-05-10 Moved SSD1306 reset into the SSD1306 component
2018-05-10 Added a few comments to main
2018-05-10 Removed all C firmware
    The rust firmware is now in more or less the same place as the C
    firmware.
2018-05-10 Added initial channel implementation
2018-05-14 Moved nb-sync into its own crate
    I think it is simple enough and appears to work well enough to release
    to people to tinker with.
2018-05-19 Fixed PWM to handle both TIM1 and TIM14
2018-05-19 First try at PID with general Process trait (does not compile)
2018-05-19 Got less ambitious and made PID operate directly on a PwmPin
2018-05-28 Changed PID to use some fixed point arithmetic
2018-06-03 Added note with conversion and amplification factors to schematic
2018-06-03 Added ADC conversion and display that assumes 3V=500C
2018-06-30 Upgraded to remove xargo and instead depend on cargo
    - Upgraded all the cortex-m packages
    - Upgraded bare-metal
    - Upgraded the svd2rust generated code
    - Changed the ISRs (mostly...SysTick is still pending) to use the new
    macro
    - Changed the hard fault handler to be more friendly
2018-06-30 Fixed the flash size to match the actual part used
2018-06-30 Fixed SysTick to be declared
    I had to add the `rt` crate to board-support so that I could get the
    exception! macro. I guess the interrupt! and exception! macros actually
    define the function, so it gets to be `pub use`d back up at main.
    The program now runs without hard faults. So difficult to figure out
    what was wrong...
